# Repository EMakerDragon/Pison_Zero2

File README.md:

## 概要
Raspberry Pi Zero 2 WをIntel Edisonサイズに収めるプロジェクトです。  
Raspberry Pi Zero 2 Wから部品をすべて移植することで作成できます。  
かなり適当な設計なので参考程度にしてください。
## 回路説明
USBでPCに接続する瞬間にJP2をオープンにすることでeMMCの電源を切断できるので、USBBOOTでeMMCへ書き込めるようになります。  
## 参考
部品名はこちらのリポジトリと同じにしています。↓  
https://github.com/iocapa/reverse-raspberrypi-zero-2w-schematic  
また、シンボルなどはこちらのリポジトリのものをKicad用に変換して使用しています。↓  
https://github.com/jonny12375/rp3a0

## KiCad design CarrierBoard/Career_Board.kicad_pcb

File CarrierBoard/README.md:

## 概要
Pison Zero 2用のキャリアボードです。
## 回路説明
キャリアボードのディスプレイのフットプリントのピンピッチが違うので修正して使用してください。

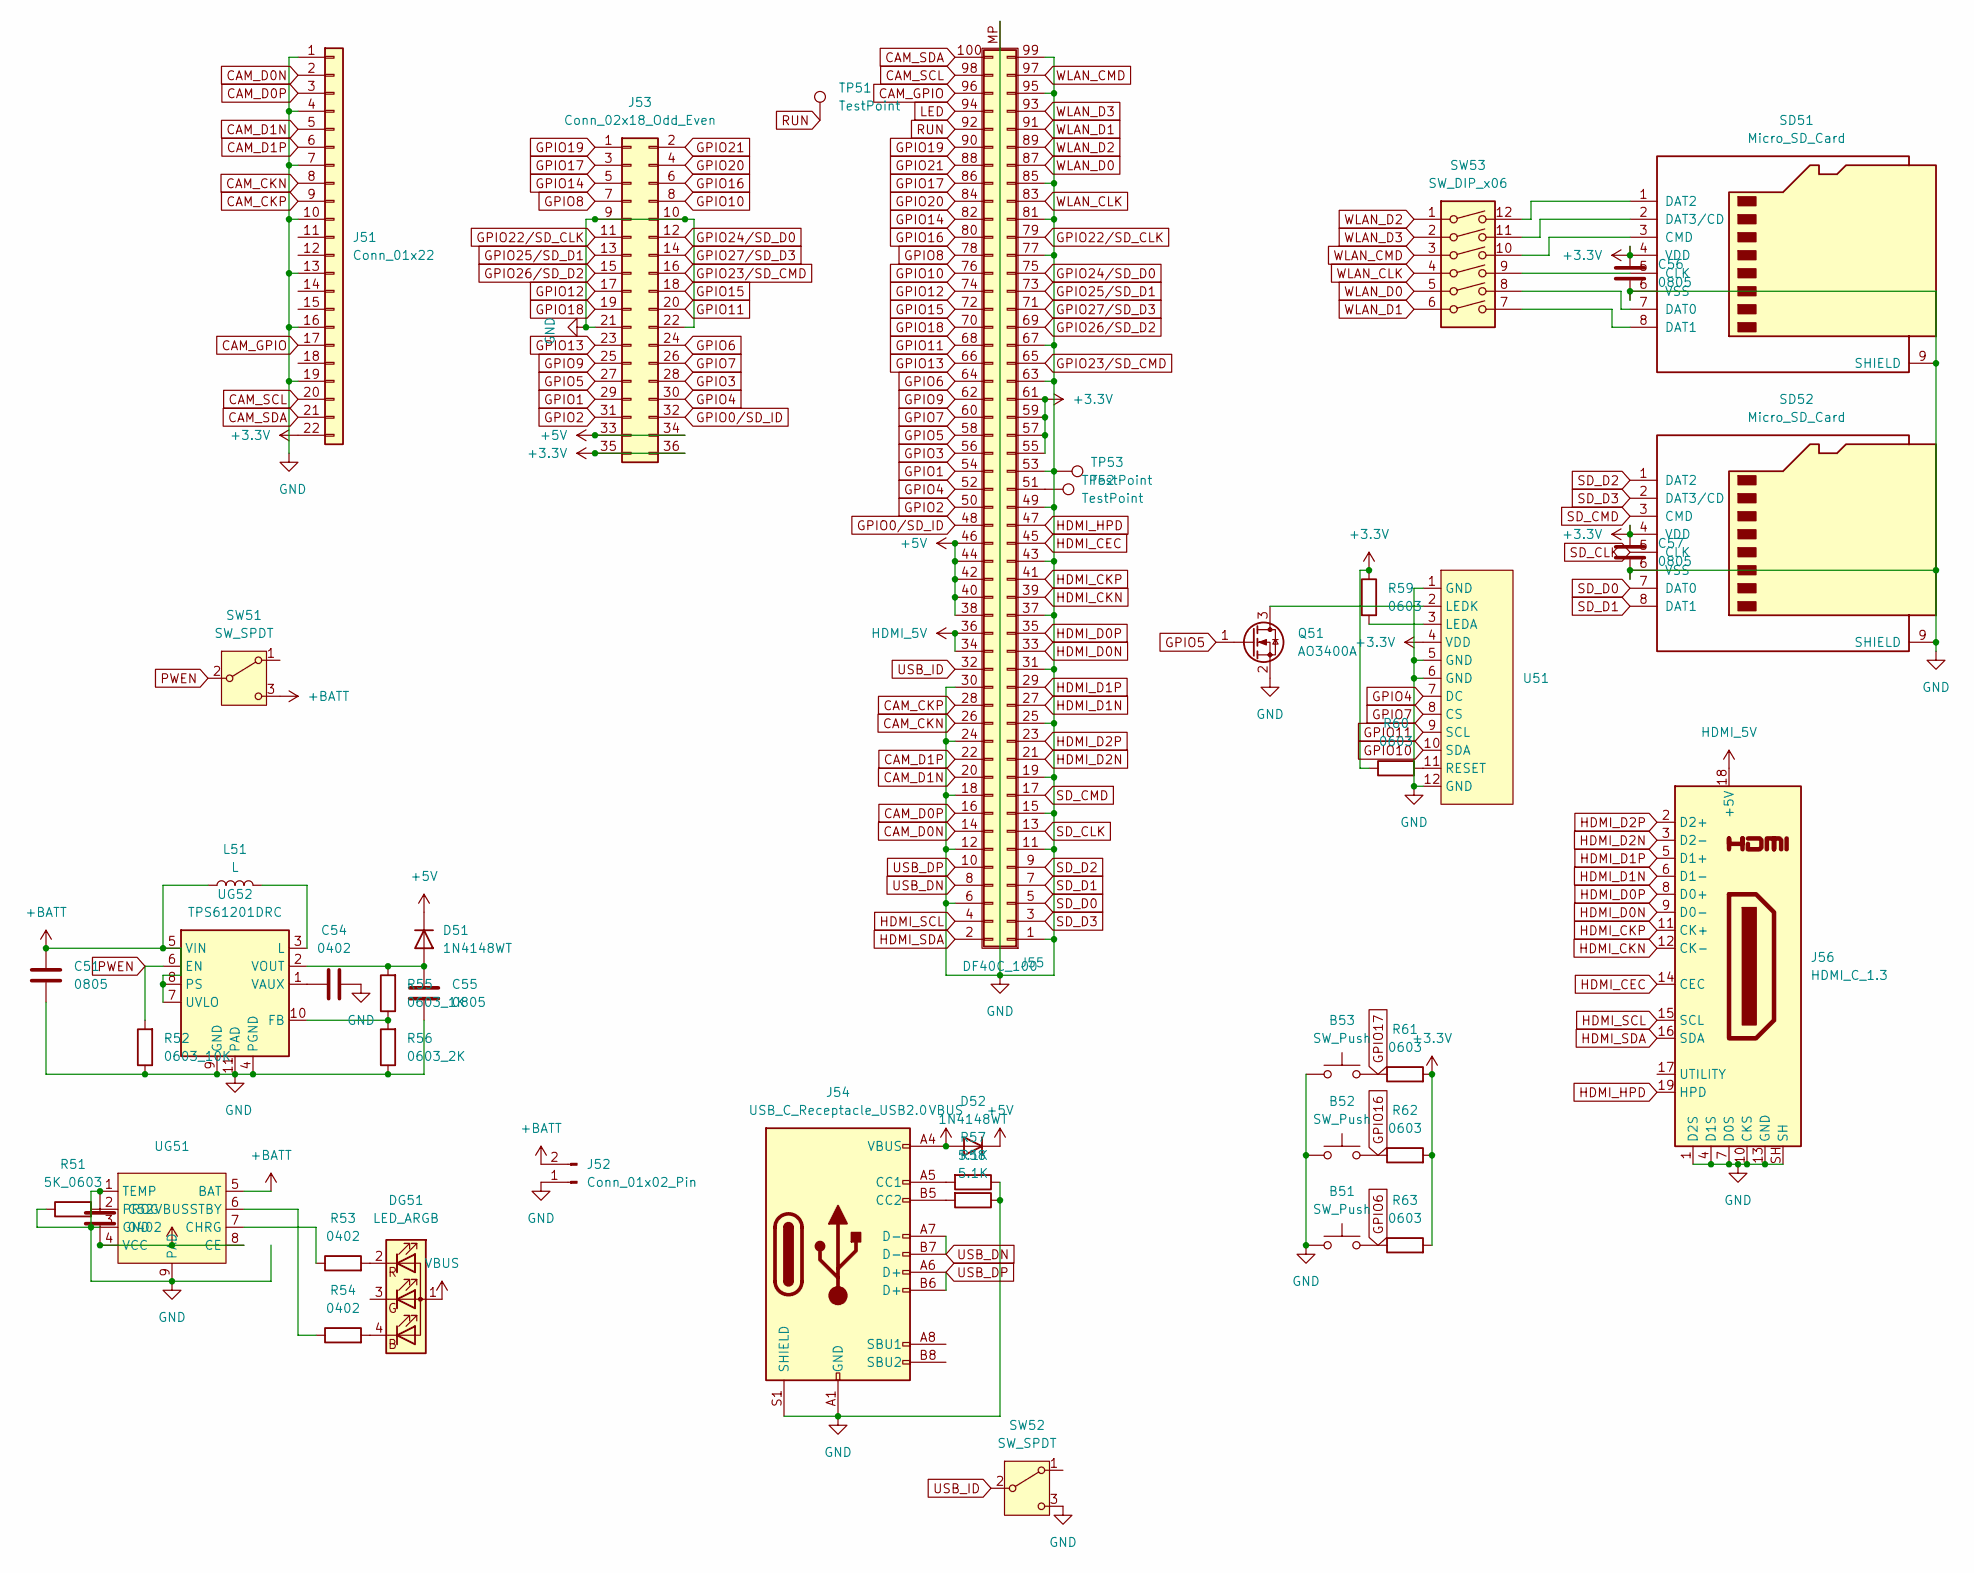
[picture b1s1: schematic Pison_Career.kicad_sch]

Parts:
B51, B52, B53: SW_Push; SKRMAAE010
C51, C55, C56, C57: 0805; C_0805_2012Metric
C52, C54: 0402; C_0402_1005Metric
D51, D52: 1N4148WT; D_SMA
DG51: LED_ARGB; LED_Wurth_150044M155260
J51: Conn_01x22; TE_2-1734839-1_1x21-1MP_P0.5mm_Horizontal
J52: Conn_01x02_Pin; PinHeader_1x02_P2.54mm_Vertical
J53: Conn_02x18_Odd_Even; PinHeader_2x18_P2.54mm_Vertical
J54: USB_C_Receptacle_USB2.0; USB_C_Receptacle_G-Switch_GT-USB-7010ASV; Part Description USBC USB2 data and power connector
J55: DF40C_100; Pison_Zero_2
J56: HDMI_C_1.3; CONN19_2013978-2_TEC
L51: L; L_Abracon_ASPI-0425
Q51: AO3400A; SOT-23
R51: 5K_0603; R_0603_1608Metric
R52: 0603_10K; R_0603_1608Metric
R53, R54: 0402; R_0402_1005Metric
R55: 0603_1K; R_0603_1608Metric
R56: 0603_2K; R_0603_1608Metric
R57, R58: 5.1K; R_0603_1608Metric
R59, R60, R61, R62, R63: 0603; R_0603_1608Metric
SD51, SD52: Micro_SD_Card; microSD_HC_Molex_104031-0811
SW51, SW52: SW_SPDT; SW_SPDT_PCM12
SW53: SW_DIP_x06; SD_JUMP
TP51, TP52, TP53: TestPoint; TestPoint_Pad_D1.5mm
U51: ST7789_2.0
UG51: SOIC-8-1EP_3.9x4.9mm_P1.27mm_EP2.29x3mm
UG52: TPS61201DRC; VSON-10-1EP_3x3mm_P0.5mm_EP1.65x2.4mm

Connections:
+5V: D51.1 (K), D52.1 (K), J53.33, J53.34, J55.38 (Pin_b19), J55.40 (Pin_b20), J55.42 (Pin_b21), J55.44 (Pin_b22), J55.46 (Pin_b23)
+BATT: C51.2, J52.2, L51.1, SW51.3 (C), UG51.5 (BAT), UG52.5 (VIN), UG52.7 (UVLO), UG52.8 (PS)
CAM_CKN: J51.8, J55.26 (Pin_b13)
CAM_CKP: J51.9, J55.28 (Pin_b14)
CAM_D0N: J51.2, J55.14 (Pin_b7)
CAM_D0P: J51.3, J55.16 (Pin_b8)
CAM_D1N: J51.5, J55.20 (Pin_b10)
CAM_D1P: J51.6, J55.22 (Pin_b11)
CAM_GPIO: J51.17, J55.96 (Pin_b48)
CAM_SCL: J51.20, J55.98 (Pin_b49)
CAM_SDA: J51.21, J55.100 (Pin_b50)
GND: B51.1, B52.1, B53.1, C51.1, C52.2, C54.2, C55.2, C56.2, C57.2, J51.1, J51.4, J51.7, J51.10, J51.13, J51.16, J51.19, J52.1, J53.9, J53.10, J53.21, J53.22, J54.A1 (GND), J54.A12 (GND), J54.B1 (GND), J54.B12 (GND), J54.S1 (SHIELD), J55.1 (Pin_a1), J55.6 (Pin_b3), J55.11 (Pin_a6), J55.12 (Pin_b6), J55.15 (Pin_a8), J55.18 (Pin_b9), J55.19 (Pin_a10), J55.24 (Pin_b12), J55.25 (Pin_a13), J55.30 (Pin_b15), J55.31 (Pin_a16), J55.37 (Pin_a19), J55.43 (Pin_a22), J55.49 (Pin_a25), J55.53 (Pin_a27), J55.63 (Pin_a32), J55.67 (Pin_a34), J55.77 (Pin_a39), J55.81 (Pin_a41), J55.85 (Pin_a43), J55.95 (Pin_a48), J55.99 (Pin_a50), J55.MP (Shield), J56.1 (D2S), J56.4 (D1S), J56.7 (D0S), J56.10 (CKS), J56.13 (GND), J56.SH, Q51.2 (S), R51.1, R52.1, R56.1, R57.1, R58.1, SD51.6 (VSS), SD51.9 (SHIELD), SD52.6 (VSS), SD52.9 (SHIELD), SW52.3 (C), TP53.1, U51.1 (GND), U51.5 (GND), U51.6 (GND), U51.12 (GND), UG51.1 (TEMP), UG51.3 (GND), UG51.9 (PAD), UG52.4 (PGND), UG52.9 (GND), UG52.11 (PAD)
GPIO0/SD_ID: J53.32, J55.48 (Pin_b24)
GPIO1: J53.29, J55.54 (Pin_b27)
GPIO2: J53.31, J55.50 (Pin_b25)
GPIO3: J53.28, J55.56 (Pin_b28)
GPIO4: J53.30, J55.52 (Pin_b26), U51.7 (DC)
GPIO5: J53.27, J55.58 (Pin_b29), Q51.1 (G)
GPIO6: B51.2, J53.24, J55.64 (Pin_b32), R63.1
GPIO7: J53.26, J55.60 (Pin_b30), U51.8 (CS)
GPIO8: J53.7, J55.78 (Pin_b39)
GPIO9: J53.25, J55.62 (Pin_b31)
GPIO10: J53.8, J55.76 (Pin_b38), U51.10 (SDA)
GPIO11: J53.20, J55.68 (Pin_b34), U51.9 (SCL)
GPIO12: J53.17, J55.74 (Pin_b37)
GPIO13: J53.23, J55.66 (Pin_b33)
GPIO14: J53.5, J55.82 (Pin_b41)
GPIO15: J53.18, J55.72 (Pin_b36)
GPIO16: B52.2, J53.6, J55.80 (Pin_b40), R62.1
GPIO17: B53.2, J53.3, J55.86 (Pin_b43), R61.1
GPIO18: J53.19, J55.70 (Pin_b35)
GPIO19: J53.1, J55.90 (Pin_b45)
GPIO20: J53.4, J55.84 (Pin_b42)
GPIO21: J53.2, J55.88 (Pin_b44)
GPIO22/SD_CLK: J53.11, J55.79 (Pin_a40)
GPIO23/SD_CMD: J53.16, J55.65 (Pin_a33)
GPIO24/SD_D0: J53.12, J55.75 (Pin_a38)
GPIO25/SD_D1: J53.13, J55.73 (Pin_a37)
GPIO26/SD_D2: J53.15, J55.69 (Pin_a35)
GPIO27/SD_D3: J53.14, J55.71 (Pin_a36)
GPIO_VREF: C56.1, C57.1, J51.22, J53.35, J53.36, J55.55 (Pin_a28), J55.57 (Pin_a29), J55.59 (Pin_a30), J55.61 (Pin_a31), R59.1, R60.1, R61.2, R62.2, R63.2, SD51.4 (VDD), SD52.4 (VDD), U51.4 (VDD)
HDMI_5V: J55.34 (Pin_b17), J55.36 (Pin_b18), J56.18 (+5V)
HDMI_CEC: J55.45 (Pin_a23), J56.14 (CEC)
HDMI_CKN: J55.39 (Pin_a20), J56.12 (CK-)
HDMI_CKP: J55.41 (Pin_a21), J56.11 (CK+)
HDMI_D0N: J55.33 (Pin_a17), J56.9 (D0-)
HDMI_D0P: J55.35 (Pin_a18), J56.8 (D0+)
HDMI_D1N: J55.27 (Pin_a14), J56.6 (D1-)
HDMI_D1P: J55.29 (Pin_a15), J56.5 (D1+)
HDMI_D2N: J55.21 (Pin_a11), J56.3 (D2-)
HDMI_D2P: J55.23 (Pin_a12), J56.2 (D2+)
HDMI_HPD: J55.47 (Pin_a24), J56.19 (HPD)
HDMI_SCL: J55.4 (Pin_b2), J56.15 (SCL)
HDMI_SDA: J55.2 (Pin_b1), J56.16 (SDA)
LED: J55.94 (Pin_b47)
unnamed: C55.1, D51.2 (A), R55.2, UG52.2 (VOUT)
unnamed: DG51.4 (BK), R54.2
unnamed: DG51.2 (RK), R53.2
unnamed: J54.A5 (CC1), R57.2
unnamed: J54.B5 (CC2), R58.2
unnamed: J55.51 (Pin_a26), TP52.1
unnamed: Q51.3 (D), U51.2 (LEDK)
unnamed: SD51.5 (CLK), SW53.9
unnamed: SD51.3 (CMD), SW53.10
unnamed: SD51.7 (DAT0), SW53.8
unnamed: SD51.8 (DAT1), SW53.7
unnamed: SD51.1 (DAT2), SW53.12
unnamed: SD51.2 (DAT3/CD), SW53.11
unnamed: R59.2, U51.3 (LEDA)
unnamed: R60.2, U51.11 (RESET)
unnamed: R53.1, UG51.7 (CHRG)
unnamed: R51.2, UG51.2 (PROG)
unnamed: R54.1, UG51.6 (STBY)
unnamed: R55.1, R56.2, UG52.10 (FB)
unnamed: L51.2, UG52.3 (L)
unnamed: C54.1, UG52.1 (VAUX)
PWEN: R52.2, SW51.2 (B), UG52.6 (EN)
RUN: J55.92 (Pin_b46), TP51.1
SD_CLK: J55.13 (Pin_a7), SD52.5 (CLK)
SD_CMD: J55.17 (Pin_a9), SD52.3 (CMD)
SD_D0: J55.5 (Pin_a3), SD52.7 (DAT0)
SD_D1: J55.7 (Pin_a4), SD52.8 (DAT1)
SD_D2: J55.9 (Pin_a5), SD52.1 (DAT2)
SD_D3: J55.3 (Pin_a2), SD52.2 (DAT3/CD)
USB_DN: J54.A7 (D-), J54.B7 (D-), J55.8 (Pin_b4)
USB_DP: J54.A6 (D+), J54.B6 (D+), J55.10 (Pin_b5)
USB_ID: J55.32 (Pin_b16), SW52.2 (B)
VBUS: C52.1, D52.2 (A), DG51.1 (A), J54.A4 (VBUS), J54.A9 (VBUS), J54.B4 (VBUS), J54.B9 (VBUS), UG51.4 (VCC), UG51.8 (CE)
WLAN_CLK: J55.83 (Pin_a42), SW53.4
WLAN_CMD: J55.97 (Pin_a49), SW53.3
WLAN_D0: J55.87 (Pin_a44), SW53.5
WLAN_D1: J55.91 (Pin_a46), SW53.6
WLAN_D2: J55.89 (Pin_a45), SW53.1
WLAN_D3: J55.93 (Pin_a47), SW53.2

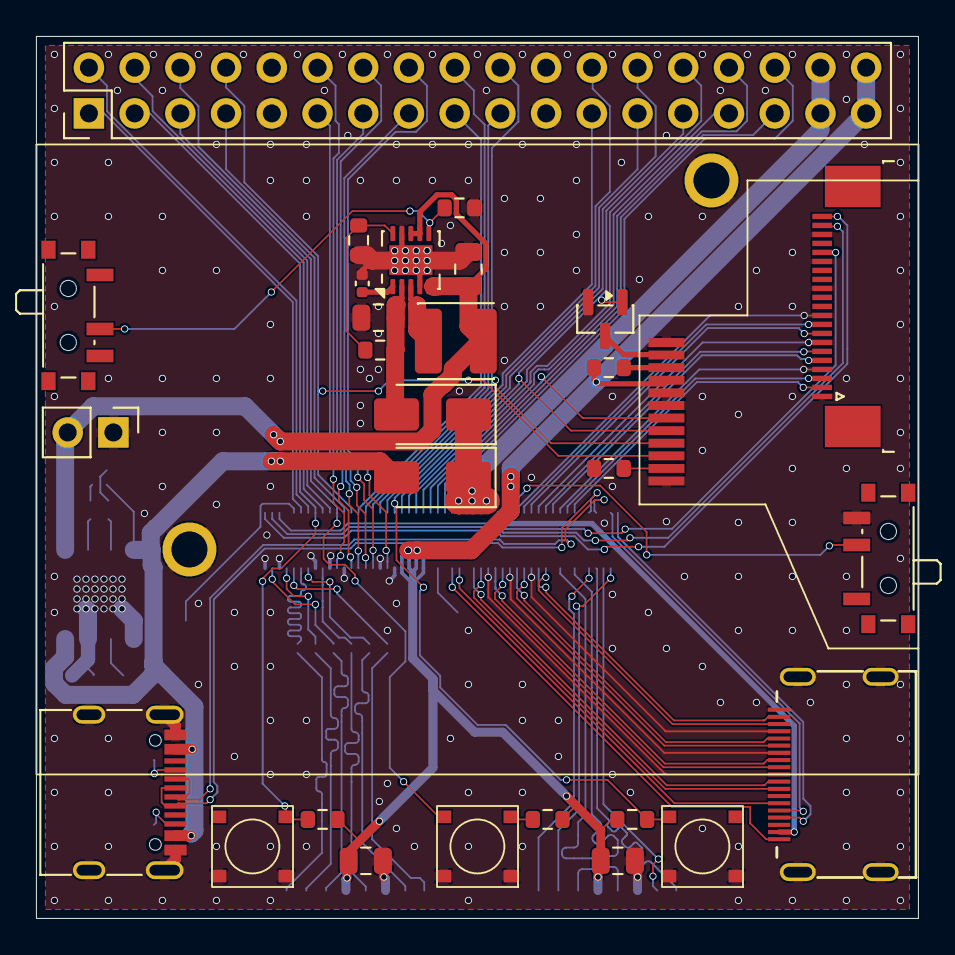
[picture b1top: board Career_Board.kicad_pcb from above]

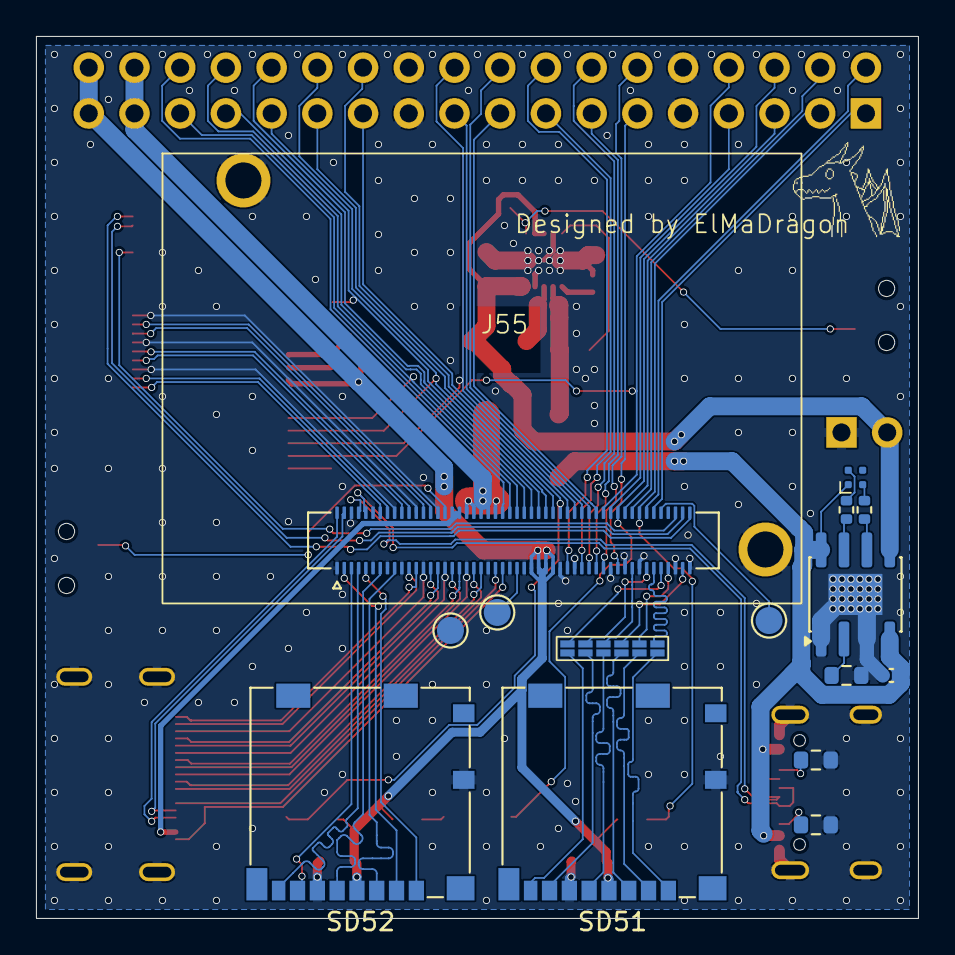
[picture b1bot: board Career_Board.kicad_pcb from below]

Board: 2 copper layers, 49.0 x 49.0 mm, 44 parts (15 on the bottom side), 93 nets.

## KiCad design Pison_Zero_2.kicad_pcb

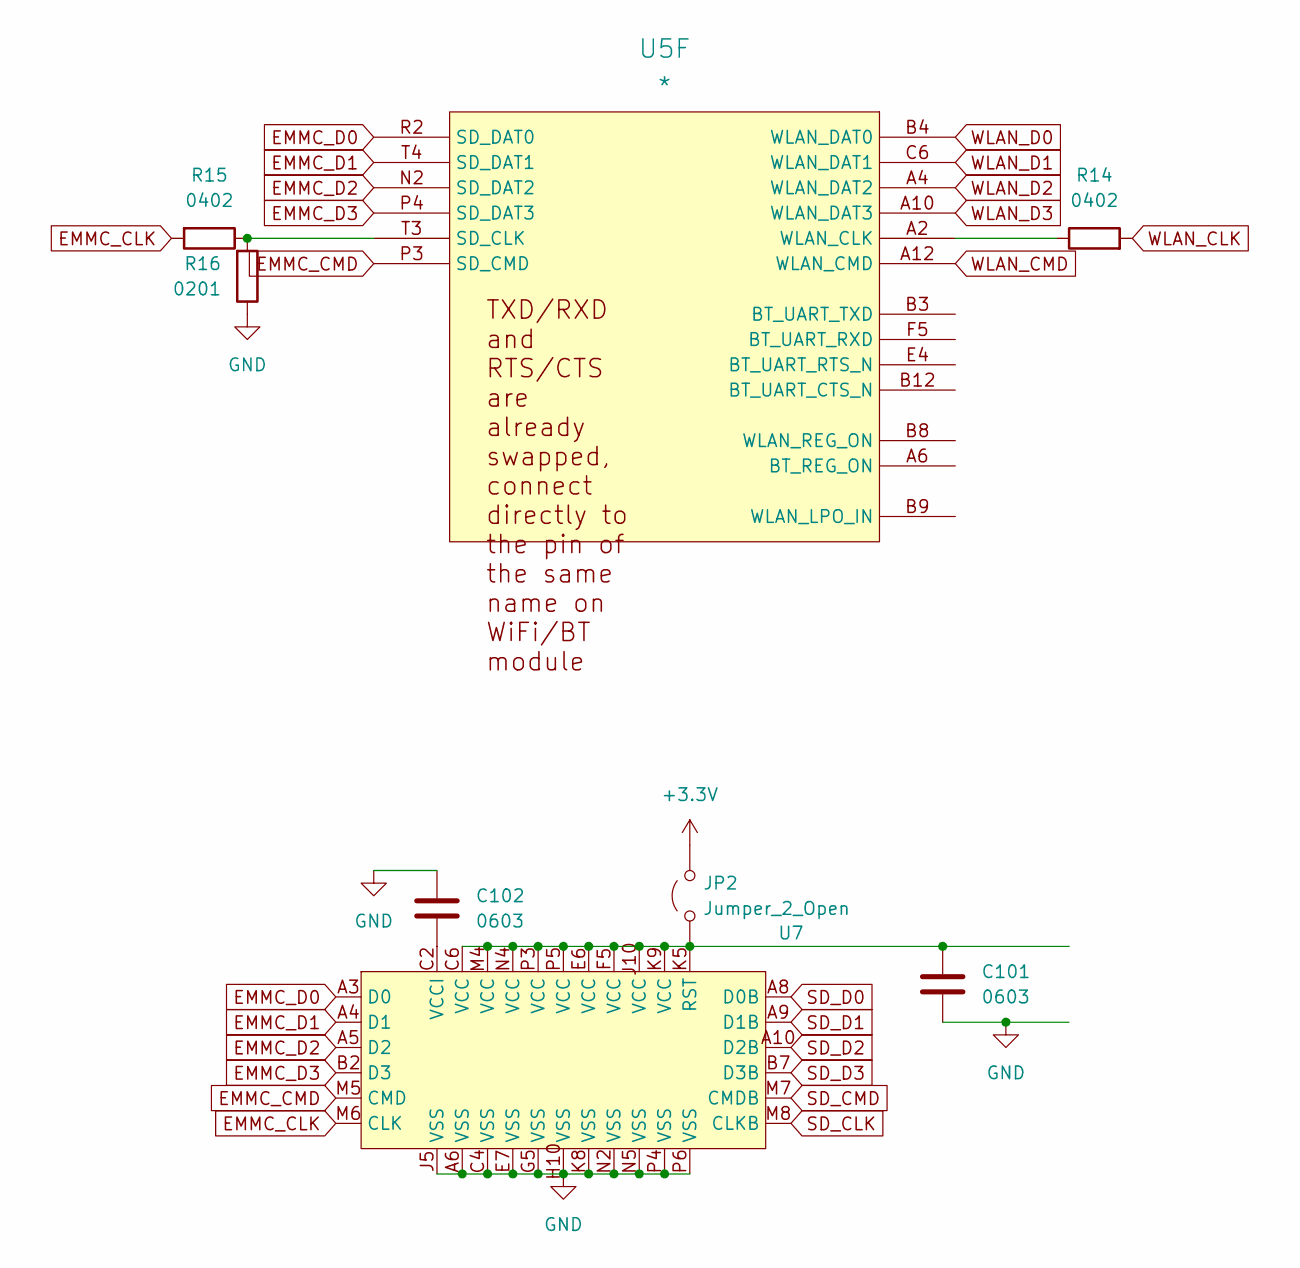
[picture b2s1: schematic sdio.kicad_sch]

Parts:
C101, C102: 0603; C_0603_1608Metric
JP2: Jumper_2_Open; SolderJumper-2_P1.3mm_Open_TrianglePad1.0x1.5mm
R14, R15: 0402; R_0402_1005Metric
R16: 0201; R_0201_0603Metric
U5: *; RP3A0-BGA
U7: LFBGA-153_11.5x13mm_Layout14x14_P0.5mm

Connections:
+3.3V: JP2.2 (B); also elsewhere on the board
EMMC_CLK: R15.2, U7.M6 (CLK)
EMMC_CMD: U5.P3 (SD_CMD), U7.M5 (CMD)
EMMC_D0: U5.R2 (SD_DAT0), U7.A3 (D0)
EMMC_D1: U5.T4 (SD_DAT1), U7.A4 (D1)
EMMC_D2: U5.N2 (SD_DAT2), U7.A5 (D2)
EMMC_D3: U5.P4 (SD_DAT3), U7.B2 (D3)
GND: C101.2, C102.1, R16.1, U7.A6 (VSS), U7.C4 (VSS), U7.E7 (VSS), U7.G5 (VSS), U7.H10 (VSS), U7.J5 (VSS), U7.K8 (VSS), U7.N2 (VSS), U7.N5 (VSS), U7.P4 (VSS), U7.P6 (VSS); also elsewhere on the board
unnamed: C101.1, JP2.1 (A), U7.C6 (VCC), U7.E6 (VCC), U7.F5 (VCC), U7.J10 (VCC), U7.K5 (RST), U7.K9 (VCC), U7.M4 (VCC), U7.N4 (VCC), U7.P3 (VCC), U7.P5 (VCC)
unnamed: R15.1, R16.2, U5.T3 (SD_CLK)
unnamed: R14.1, U5.A2 (WLAN_CLK)
unnamed: C102.2, U7.C2 (VCCI)
SD_CLK: U7.M8 (CLKB); also elsewhere on the board
SD_CMD: U7.M7 (CMDB); also elsewhere on the board
SD_D0: U7.A8 (D0B); also elsewhere on the board
SD_D1: U7.A9 (D1B); also elsewhere on the board
SD_D2: U7.A10 (D2B); also elsewhere on the board
SD_D3: U7.B7 (D3B); also elsewhere on the board
WLAN_CLK: R14.2; also elsewhere on the board
WLAN_CMD: U5.A12 (WLAN_CMD); also elsewhere on the board
WLAN_D0: U5.B4 (WLAN_DAT0); also elsewhere on the board
WLAN_D1: U5.C6 (WLAN_DAT1); also elsewhere on the board
WLAN_D2: U5.A4 (WLAN_DAT2); also elsewhere on the board
WLAN_D3: U5.A10 (WLAN_DAT3); also elsewhere on the board

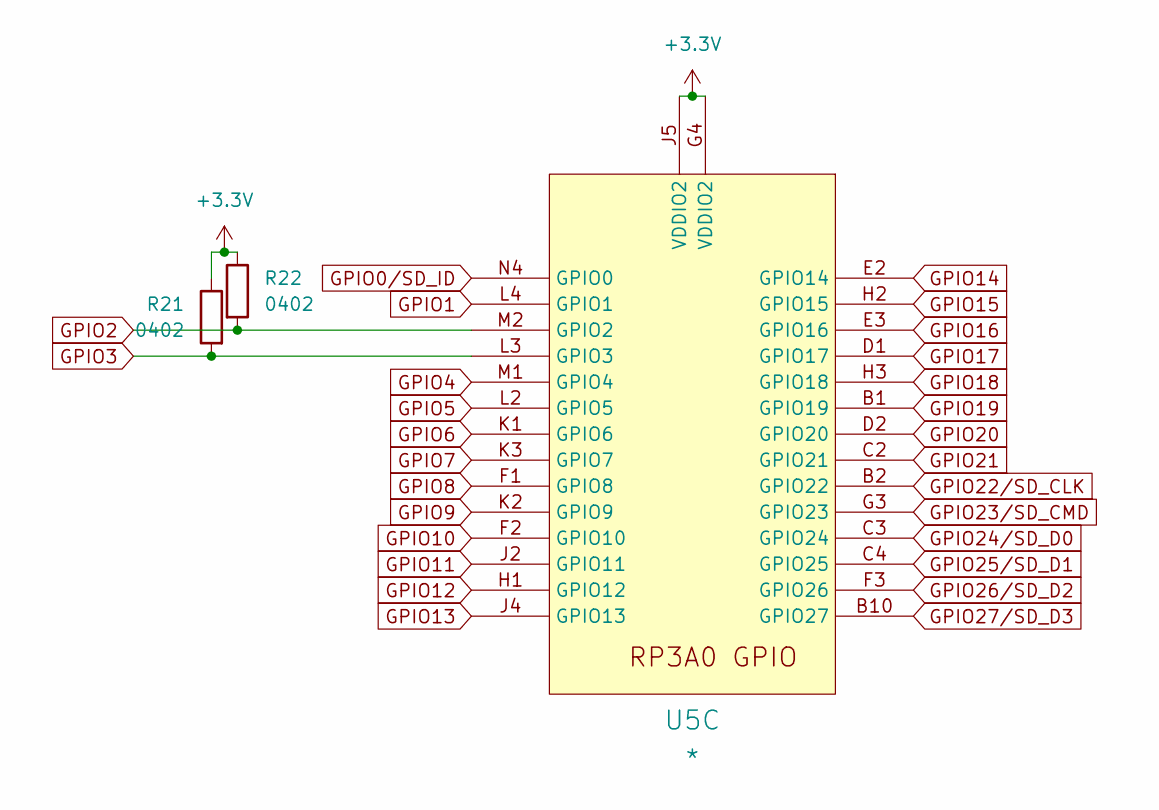
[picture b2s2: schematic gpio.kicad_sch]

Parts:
R21, R22: 0402; R_0402_1005Metric
U5: *; RP3A0-BGA

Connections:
+3.3V: R21.1, R22.1, U5.G4 (VDDIO2), U5.J5 (VDDIO2); also elsewhere on the board
GPIO0/SD_ID: U5.N4 (GPIO0); also elsewhere on the board
GPIO1: U5.L4 (GPIO1); also elsewhere on the board
GPIO2: R22.2, U5.M2 (GPIO2); also elsewhere on the board
GPIO3: R21.2, U5.L3 (GPIO3); also elsewhere on the board
GPIO4: U5.M1 (GPIO4); also elsewhere on the board
GPIO5: U5.L2 (GPIO5); also elsewhere on the board
GPIO6: U5.K1 (GPIO6); also elsewhere on the board
GPIO7: U5.K3 (GPIO7); also elsewhere on the board
GPIO8: U5.F1 (GPIO8); also elsewhere on the board
GPIO9: U5.K2 (GPIO9); also elsewhere on the board
GPIO10: U5.F2 (GPIO10); also elsewhere on the board
GPIO11: U5.J2 (GPIO11); also elsewhere on the board
GPIO12: U5.H1 (GPIO12); also elsewhere on the board
GPIO13: U5.J4 (GPIO13); also elsewhere on the board
GPIO14: U5.E2 (GPIO14); also elsewhere on the board
GPIO15: U5.H2 (GPIO15); also elsewhere on the board
GPIO16: U5.E3 (GPIO16); also elsewhere on the board
GPIO17: U5.D1 (GPIO17); also elsewhere on the board
GPIO18: U5.H3 (GPIO18); also elsewhere on the board
GPIO19: U5.B1 (GPIO19); also elsewhere on the board
GPIO20: U5.D2 (GPIO20); also elsewhere on the board
GPIO21: U5.C2 (GPIO21); also elsewhere on the board
GPIO22/SD_CLK: U5.B2 (GPIO22); also elsewhere on the board
GPIO23/SD_CMD: U5.G3 (GPIO23); also elsewhere on the board
GPIO24/SD_D0: U5.C3 (GPIO24); also elsewhere on the board
GPIO25/SD_D1: U5.C4 (GPIO25); also elsewhere on the board
GPIO26/SD_D2: U5.F3 (GPIO26); also elsewhere on the board
GPIO27/SD_D3: U5.B10 (GPIO27); also elsewhere on the board

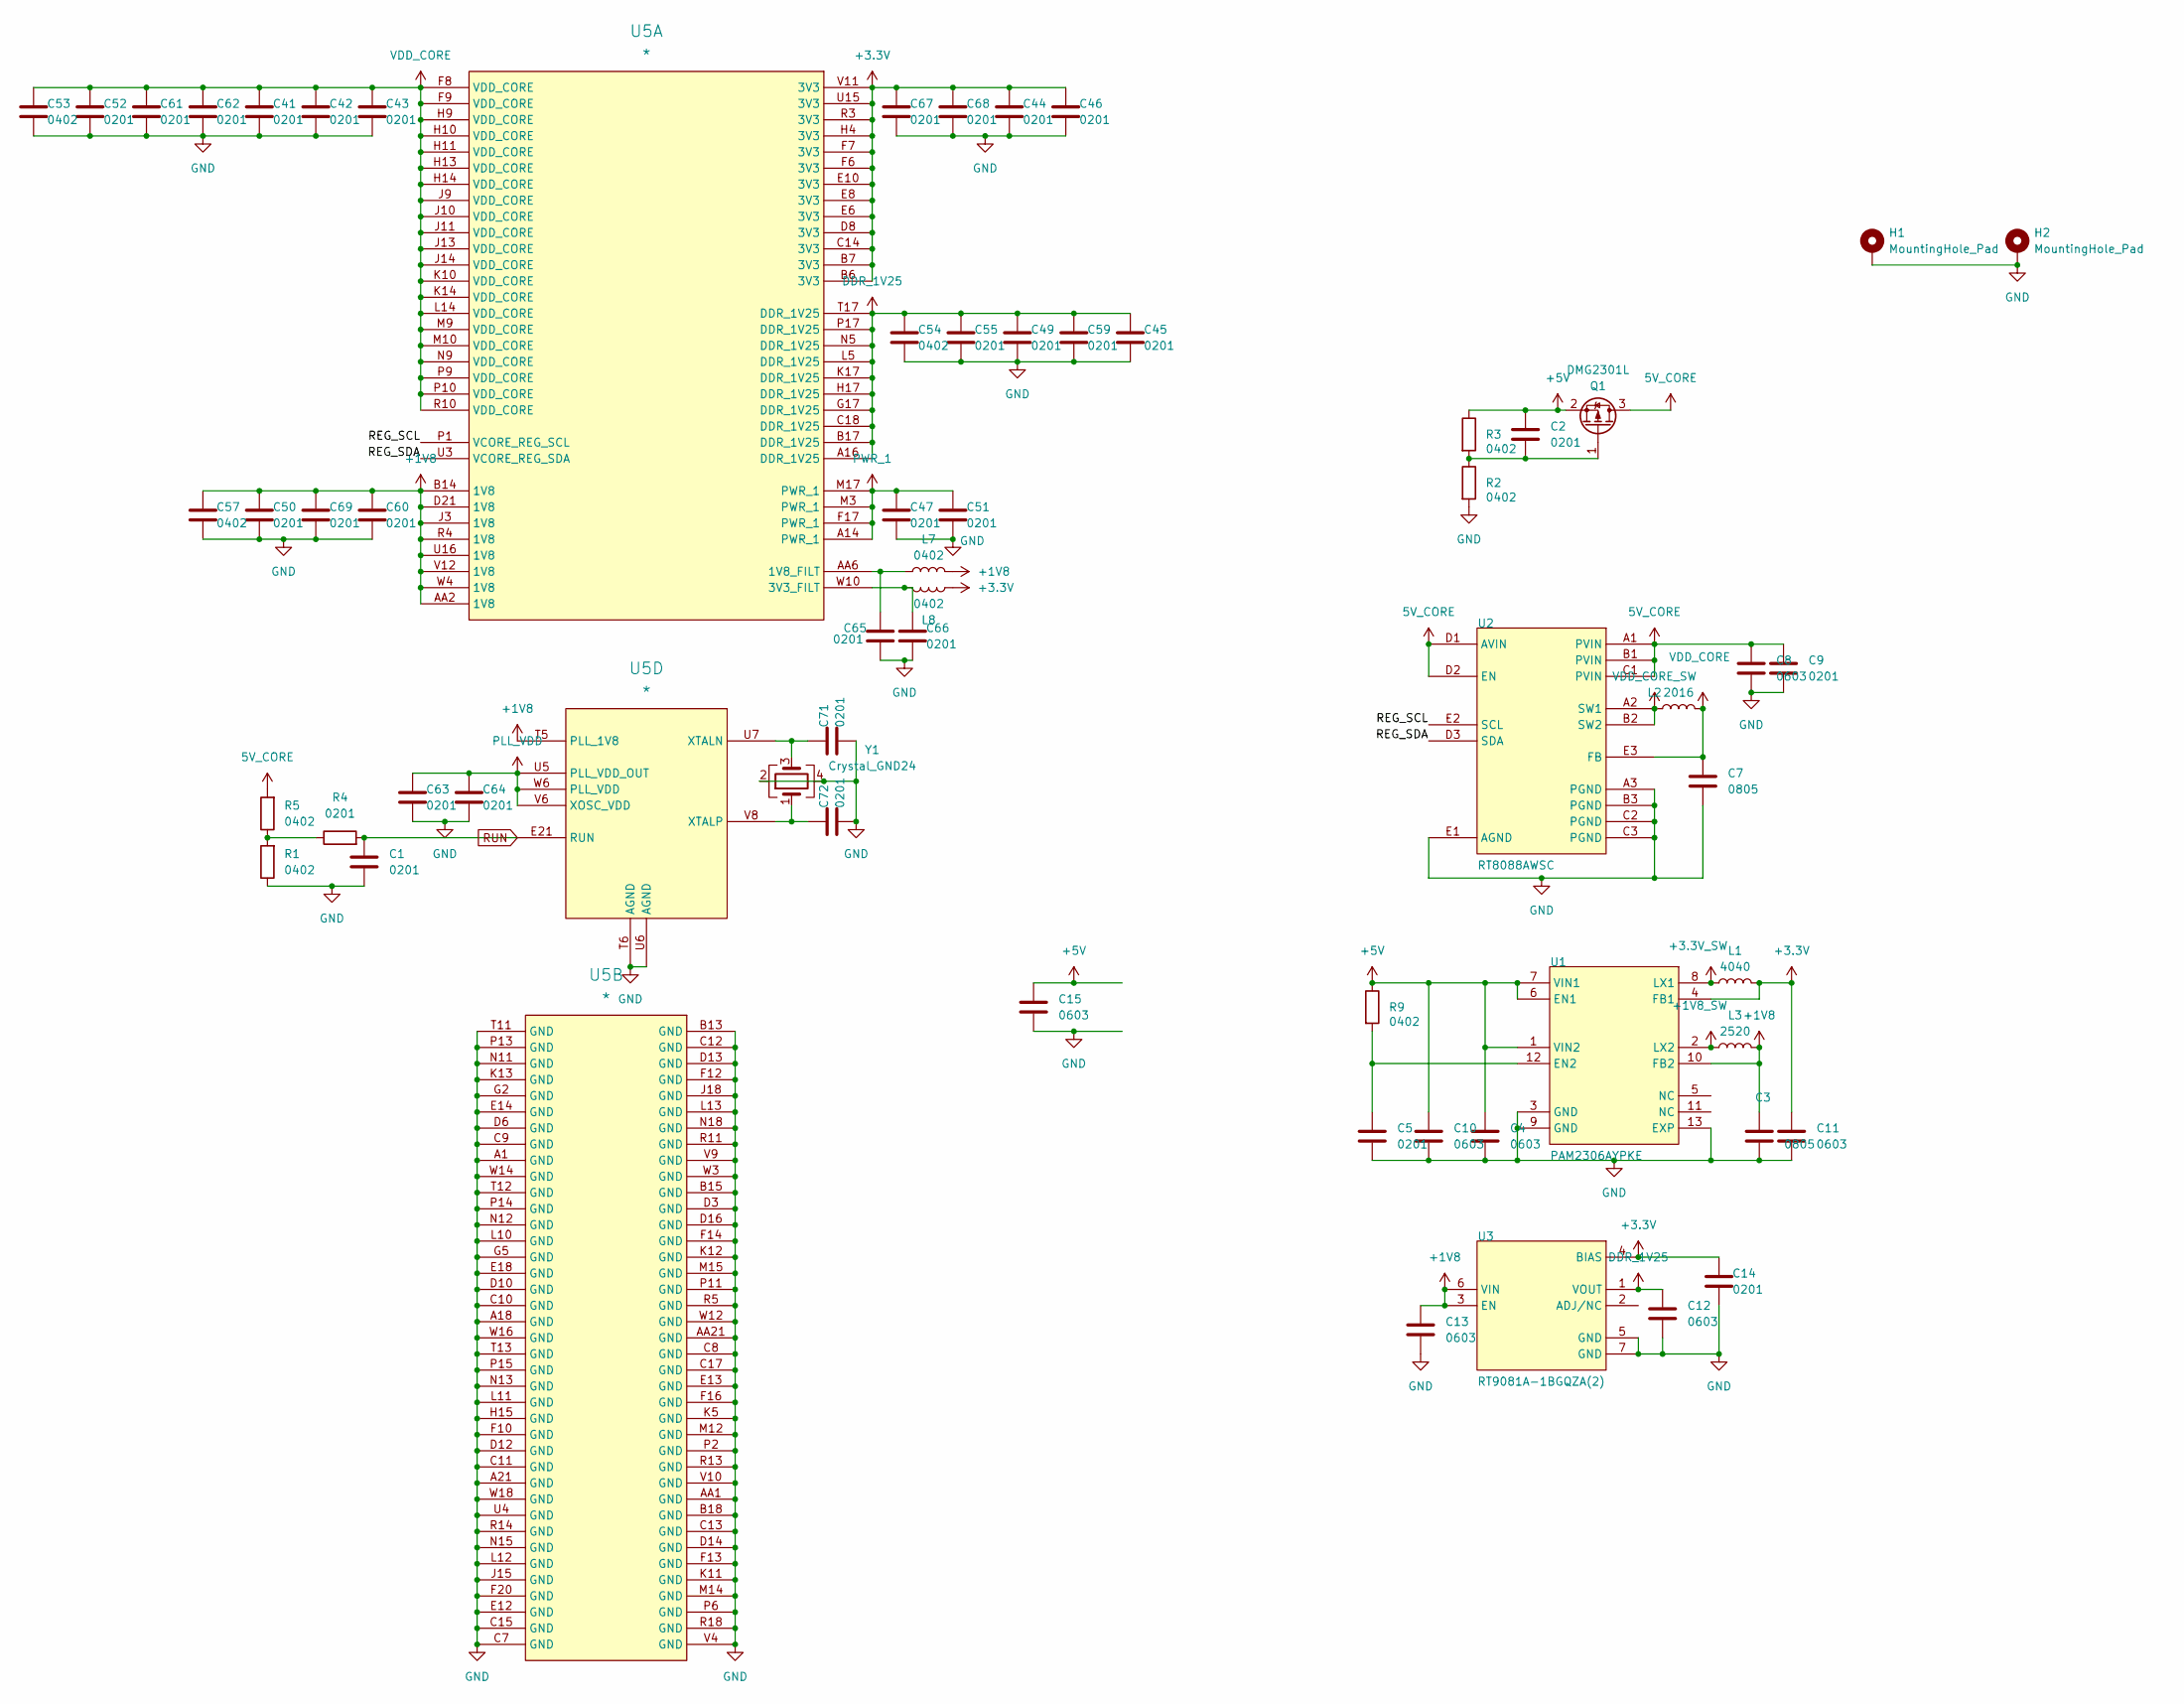
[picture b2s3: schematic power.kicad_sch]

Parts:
C1, C2, C5, C9, C14, C41, C42, C43, C44, C45, C46, C47, C49, C50, C51, C52, C55, C59, C60, C61, C62, C63, C64, C65, C66, C67, C68, C69: 0201; C_0201_0603Metric
C3, C7: 0805; C_0805_2012Metric
C4, C8, C10, C11, C12, C13, C15: 0603; C_0603_1608Metric
C53, C54, C57: 0402; C_0402_1005Metric
C71, C72: 0201; C_0402_1005Metric
H1, H2: MountingHole_Pad; EDISON_HOLE
L1: 4040; L_APV_ANR4010
L2: 2016; L_Changjiang_FTC201607S
L3: 2520; L_APV_ANR252010
L7, L8: 0402; L_0402_1005Metric
Q1: DMG2301L; SOT-23
R1, R2, R3, R5, R9: 0402; R_0402_1005Metric
R4: 0201; R_0201_0603Metric
U1: PAM2306AYPKE; SON45P300X300X80-13N
U2: RT8088AWSC; 15B_WLCSP_1.31X2.11
U3: RT9081A-1BGQZA(2); VREG_RT9081A_1BGQZA(2)
U5: *; RP3A0-BGA
Y1: Crystal_GND24; Crystal_SMD_SeikoEpson_TSX3225-4Pin_3.2x2.5mm

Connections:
5V_CORE: C8.1, C9.1, Q1.3 (D), R5.2, U2.A1 (PVIN), U2.B1 (PVIN), U2.C1 (PVIN), U2.D1 (AVIN), U2.D2 (EN)
+1V8: C3.1, C13.1, C50.1, C57.1, C60.1, C69.1, L3.2, L7.2, U1.10 (FB2), U3.3 (EN), U3.6 (VIN), U5.AA2 (1V8), U5.B14 (1V8), U5.D21 (1V8), U5.J3 (1V8), U5.R4 (1V8), U5.T5 (PLL_1V8), U5.U16 (1V8), U5.V12 (1V8), U5.W4 (1V8)
+1V8_SW: L3.1, U1.2 (LX2)
+3.3V: C11.1, C14.1, C44.1, C46.1, C67.1, C68.1, L1.2, L8.2, U1.4 (FB1), U3.4 (BIAS), U5.B6 (3V3), U5.B7 (3V3), U5.C14 (3V3), U5.D8 (3V3), U5.E6 (3V3), U5.E8 (3V3), U5.E10 (3V3), U5.F6 (3V3), U5.F7 (3V3), U5.H4 (3V3), U5.R3 (3V3), U5.U15 (3V3), U5.V11 (3V3); also elsewhere on the board
+3.3V_SW: L1.1, U1.8 (LX1)
+5V: C2.1, C4.1, C10.1, C15.1, Q1.2 (S), R3.1, R9.1, U1.1 (VIN2), U1.6 (EN1), U1.7 (VIN1); also elsewhere on the board
/Power/REG_SCL: U2.E2 (SCL), U5.P1 (VCORE_REG_SCL)
/Power/REG_SDA: U2.D3 (SDA), U5.U3 (VCORE_REG_SDA)
DDR_1V25: C12.1, C45.1, C49.1, C54.1, C55.1, C59.1, U3.1 (VOUT), U5.A16 (DDR_1V25), U5.B17 (DDR_1V25), U5.C18 (DDR_1V25), U5.G17 (DDR_1V25), U5.H17 (DDR_1V25), U5.K17 (DDR_1V25), U5.L5 (DDR_1V25), U5.N5 (DDR_1V25), U5.P17 (DDR_1V25), U5.T17 (DDR_1V25)
GND: C1.2, C3.2, C4.2, C5.2, C7.2, C8.2, C9.2, C10.2, C11.2, C12.2, C13.2, C14.2, C15.2, C41.2, C42.2, C43.2, C44.2, C45.2, C46.2, C47.2, C49.2, C50.2, C51.2, C52.2, C53.2, C54.2, C55.2, C57.2, C59.2, C60.2, C61.2, C62.2, C63.2, C64.2, C65.2, C66.2, C67.2, C68.2, C69.2, C71.2, C72.2, H1.1, H2.1, R1.1, R2.2, U1.3 (GND), U1.9 (GND), U1.13 (EXP), U2.A3 (PGND), U2.B3 (PGND), U2.C2 (PGND), U2.C3 (PGND), U2.E1 (AGND), U3.5 (GND), U3.7 (GND), U5.A1 (GND), U5.A18 (GND), U5.A21 (GND), U5.AA1 (GND), U5.AA21 (GND), U5.B13 (GND), U5.B15 (GND), U5.B18 (GND), U5.C7 (GND), U5.C8 (GND), U5.C9 (GND), U5.C10 (GND), U5.C11 (GND), U5.C12 (GND), U5.C13 (GND), U5.C15 (GND), U5.C17 (GND), U5.D3 (GND), U5.D6 (GND), U5.D10 (GND), U5.D12 (GND), U5.D13 (GND), U5.D14 (GND), U5.D16 (GND), U5.E12 (GND), U5.E13 (GND), U5.E14 (GND), U5.E18 (GND), U5.F10 (GND), U5.F12 (GND), U5.F13 (GND), U5.F14 (GND), U5.F16 (GND), U5.F20 (GND), U5.G2 (GND), U5.G5 (GND), U5.H15 (GND), U5.J15 (GND), U5.J18 (GND), U5.K5 (GND), U5.K11 (GND), U5.K12 (GND), U5.K13 (GND), U5.L10 (GND), U5.L11 (GND), U5.L12 (GND), U5.L13 (GND), U5.M12 (GND), U5.M14 (GND), U5.M15 (GND), U5.N11 (GND), U5.N12 (GND), U5.N13 (GND), U5.N15 (GND), U5.N18 (GND), U5.P2 (GND), U5.P6 (GND), U5.P11 (GND), U5.P13 (GND), U5.P14 (GND), U5.P15 (GND), U5.R5 (GND), U5.R11 (GND), U5.R13 (GND), U5.R14 (GND), U5.R18 (GND), U5.T6 (AGND), U5.T11 (GND), U5.T12 (GND), U5.T13 (GND), U5.U4 (GND), U5.U6 (AGND), U5.V4 (GND), U5.V9 (GND), U5.V10 (GND), U5.W3 (GND), U5.W12 (GND), U5.W14 (GND), U5.W16 (GND), U5.W18 (GND), Y1.2, Y1.4; also elsewhere on the board
unnamed: C2.2, Q1.1 (G), R2.1, R3.2
unnamed: R1.2, R4.1, R5.1
unnamed: C5.1, R9.2, U1.12 (EN2)
unnamed: C65.1, L7.1, U5.AA6 (1V8_FILT)
unnamed: C66.1, L8.1, U5.W10 (3V3_FILT)
unnamed: C71.1, U5.U7 (XTALN), Y1.3
unnamed: C72.1, U5.V8 (XTALP), Y1.1
PLL_VDD: C63.1, C64.1, U5.U5 (PLL_VDD_OUT), U5.V6 (XOSC_VDD), U5.W6 (PLL_VDD)
PWR_1: C47.1, C51.1, U5.A14 (PWR_1), U5.F17 (PWR_1), U5.M3 (PWR_1), U5.M17 (PWR_1)
RUN: C1.1, R4.2, U5.E21 (RUN); also elsewhere on the board
VDD_CORE: C7.1, C41.1, C42.1, C43.1, C52.1, C53.1, C61.1, C62.1, L2.2, U2.E3 (FB), U5.F8 (VDD_CORE), U5.F9 (VDD_CORE), U5.H9 (VDD_CORE), U5.H10 (VDD_CORE), U5.H11 (VDD_CORE), U5.H13 (VDD_CORE), U5.H14 (VDD_CORE), U5.J9 (VDD_CORE), U5.J10 (VDD_CORE), U5.J11 (VDD_CORE), U5.J13 (VDD_CORE), U5.J14 (VDD_CORE), U5.K10 (VDD_CORE), U5.K14 (VDD_CORE), U5.L14 (VDD_CORE), U5.M9 (VDD_CORE), U5.M10 (VDD_CORE), U5.N9 (VDD_CORE), U5.P9 (VDD_CORE), U5.P10 (VDD_CORE), U5.R10 (VDD_CORE)
VDD_CORE_SW: L2.1, U2.A2 (SW1), U2.B2 (SW2)

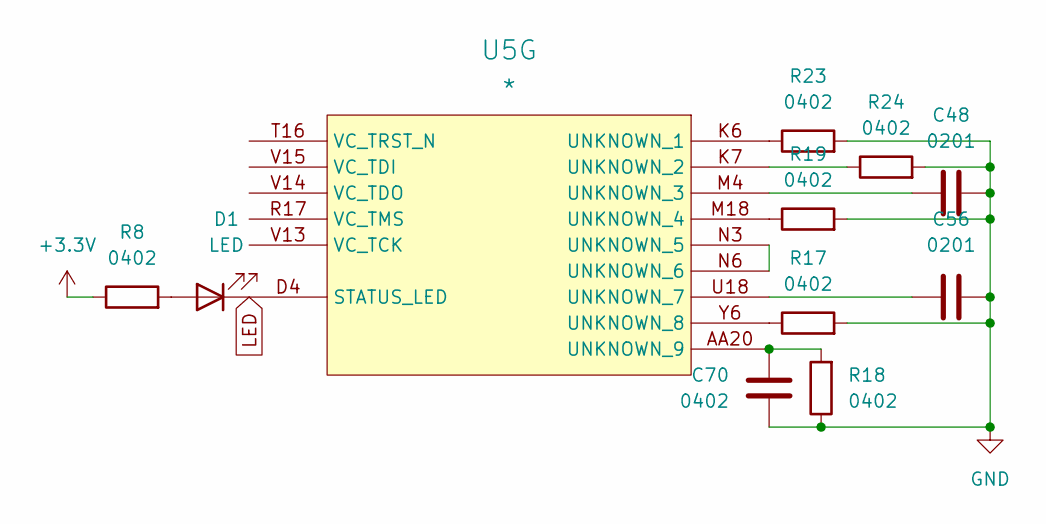
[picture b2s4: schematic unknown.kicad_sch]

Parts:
C48, C56: 0201; C_0201_0603Metric
C70: 0402; C_0402_1005Metric
D1: LED; LED_0603_1608Metric
R8, R17, R18, R19, R23, R24: 0402; R_0402_1005Metric
U5: *; RP3A0-BGA

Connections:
+3.3V: R8.1; also elsewhere on the board
GND: C48.2, C56.2, C70.1, R17.2, R18.1, R19.2, R23.2, R24.2; also elsewhere on the board
LED: D1.1 (K), U5.D4 (STATUS_LED); also elsewhere on the board
unnamed: D1.2 (A), R8.2
unnamed: R23.1, U5.K6 (UNKNOWN_1)
unnamed: R24.1, U5.K7 (UNKNOWN_2)
unnamed: C48.1, U5.M4 (UNKNOWN_3)
unnamed: R19.1, U5.M18 (UNKNOWN_4)
unnamed: U5.N3 (UNKNOWN_5), U5.N6 (UNKNOWN_6)
unnamed: C56.1, U5.U18 (UNKNOWN_7)
unnamed: R17.1, U5.Y6 (UNKNOWN_8)
unnamed: C70.2, R18.2, U5.AA20 (UNKNOWN_9)
